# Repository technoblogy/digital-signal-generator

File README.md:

# Digital Signal Generator
A digital signal generator, based on an AVR16EB28, that generates a crystal accurate square wave of from 2Hz to 33.5MHz in precise steps of 2Hz. You can enter an exact frequency, or adjust the frequency continuously using a rotary encoder.

See http://www.technoblogy.com/show?5QE2.

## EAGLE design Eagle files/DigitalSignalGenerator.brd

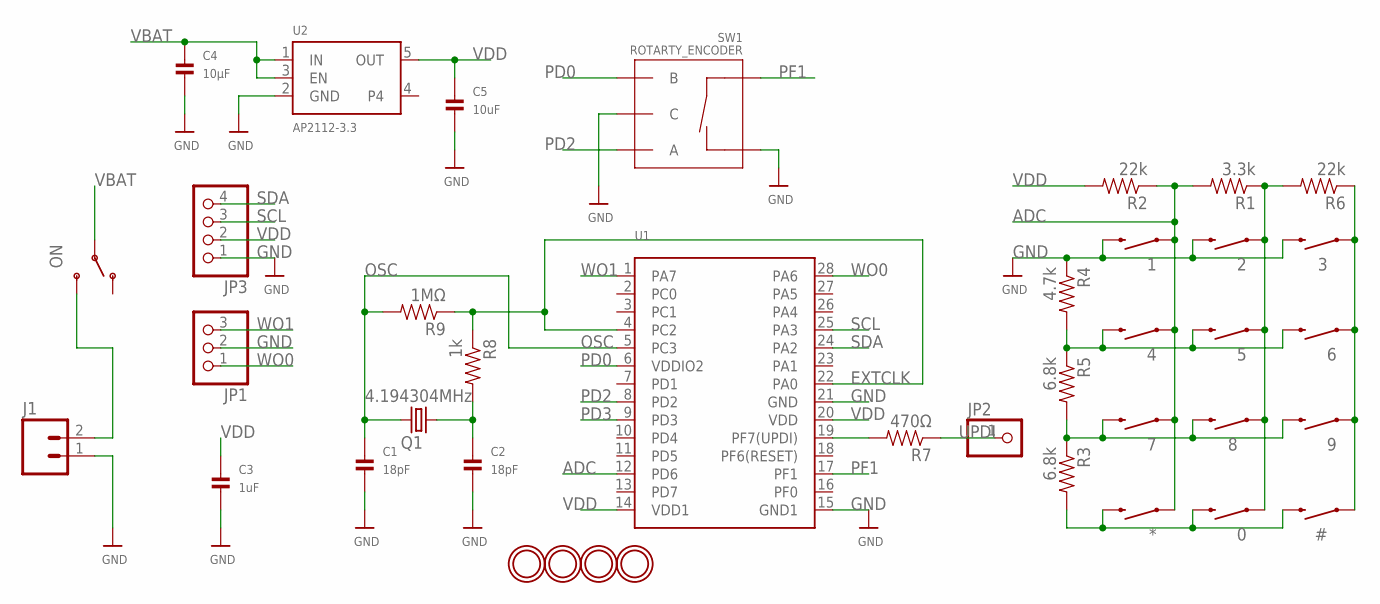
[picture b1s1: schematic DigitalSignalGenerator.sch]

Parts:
0, 1, 2, 3, 4, 5, 6, 7, 8, 9: SWITCH-MOMENTARY-2PTH; TACTILE-PTH
#: SWITCH-MOMENTARY-2PTH; TACTILE-PTH
*: SWITCH-MOMENTARY-2PTH; TACTILE-PTH
C1, C2: 18pF; _0805MP
C3: 1uF; _0805MP
C4: 10µF; _0805MP
C5: 10uF; _0805MP
J1: M02JST-PTH-VERT; JST-2-PTH-VERT
JP1: HEADER-1X3ROUND; 1X03_ROUND
JP2: PINHD-1X1CB; 1X01-CLEANBIG
JP3: HEADER-1X4ROUND; 1X04_ROUND
ON: SWITCH-SPDTKIT; SWITCH-SPDT_KIT
Q1: 4.194304MHz; CSM-7X-DU
R1: 3.3k; 0805
R2, R6: 22k; 0805
R3, R5: 6.8k; 0805
R4: 4.7k; 0805
R7: 470Ω; 0805
R8: 1k; 0805
R9: 1MΩ; 0805
SW1: ROTARTY_ENCODER; ROTARY_ENC_PLAIN
U1: AVR64DD28SSOPSSOP28; SSOP28DB
U2: AP2112-3.3; SOT23-5
U$9, U$10, U$11, U$12: MOUNTINGHOLE2.5; MOUNTINGHOLE_2.5_PLATED

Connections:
ADC: 1.1, 4.1, 7.1, *.1, R1.2, R2.1, U1.12 (PD6)
EXTCLK: R8.1, R9.1, U1.4 (PC2), U1.22 (PA0)
GND: 1.3 (2), 2.3 (2), 3.3 (2), C1.2, C2.2, C3.2, C4.2, C5.2, J1.1, JP1.2, JP3.1, R4.1, SW1.C, SW1.SW-, U1.15 (GND1), U1.21 (GND), U2.2 (GND)
unnamed: R7.2, U1.19 (PF7(UPDI))
unnamed: C2.1, Q1.2, R8.2
unnamed: J1.2, ON.3 (S)
unnamed: 0.3 (2), #.3 (2), *.3 (2), R3.2
unnamed: 4.3 (2), 5.3 (2), 6.3 (2), R4.2, R5.1
unnamed: 7.3 (2), 8.3 (2), 9.3 (2), R3.1, R5.2
unnamed: 0.1, 2.1, 5.1, 8.1, R1.1, R6.2
unnamed: 3.1, 6.1, 9.1, #.1, R6.1
OSC: C1.1, Q1.1, R9.2, U1.5 (PC3)
PD0: SW1.B, U1.6 (VDDIO2)
PD2: SW1.A, U1.8 (PD2)
PD3: U1.9 (PD3)
PF1: SW1.SW+, U1.17 (PF1)
SCL: JP3.3, U1.25 (PA3)
SDA: JP3.4, U1.24 (PA2)
UPDI: JP2.1, R7.1
VBAT: C4.1, ON.2, U2.1 (IN), U2.3 (EN)
VDD: C3.1, C5.1, JP3.2, R2.2, U1.14 (VDD1), U1.20 (VDD), U2.5 (OUT)
WO0: JP1.1, U1.28 (PA6)
WO1: JP1.3, U1.1 (PA7)

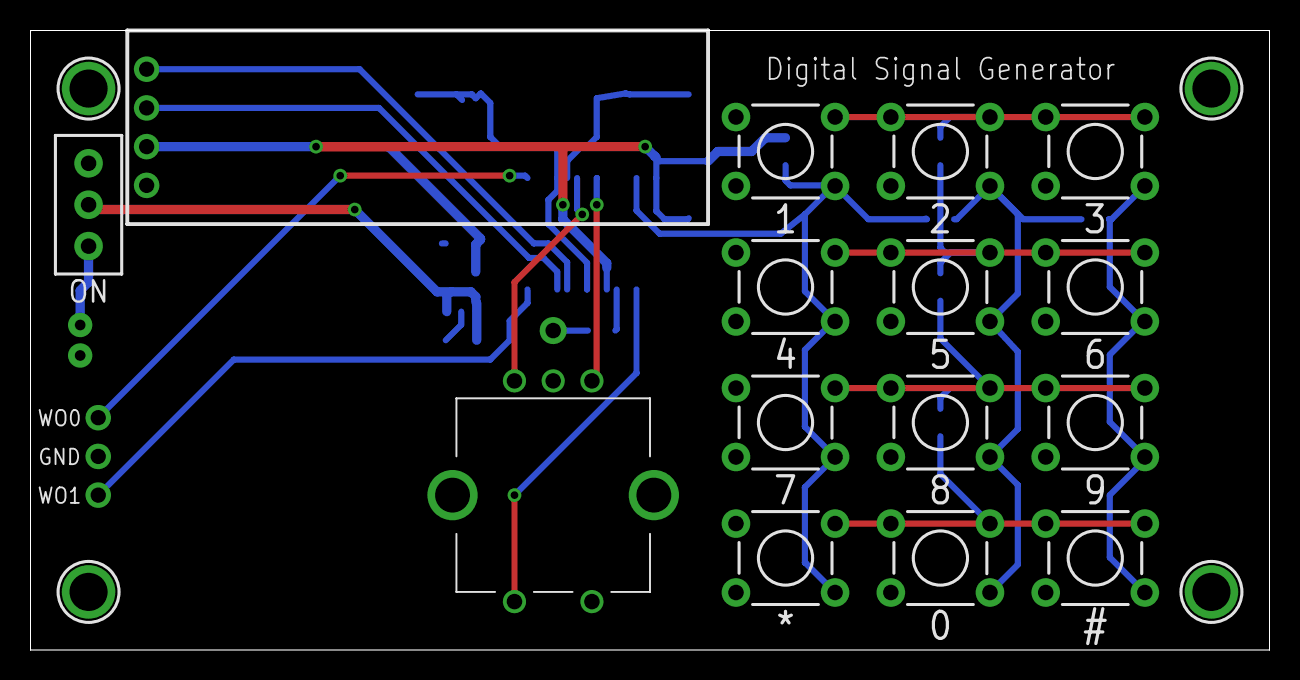
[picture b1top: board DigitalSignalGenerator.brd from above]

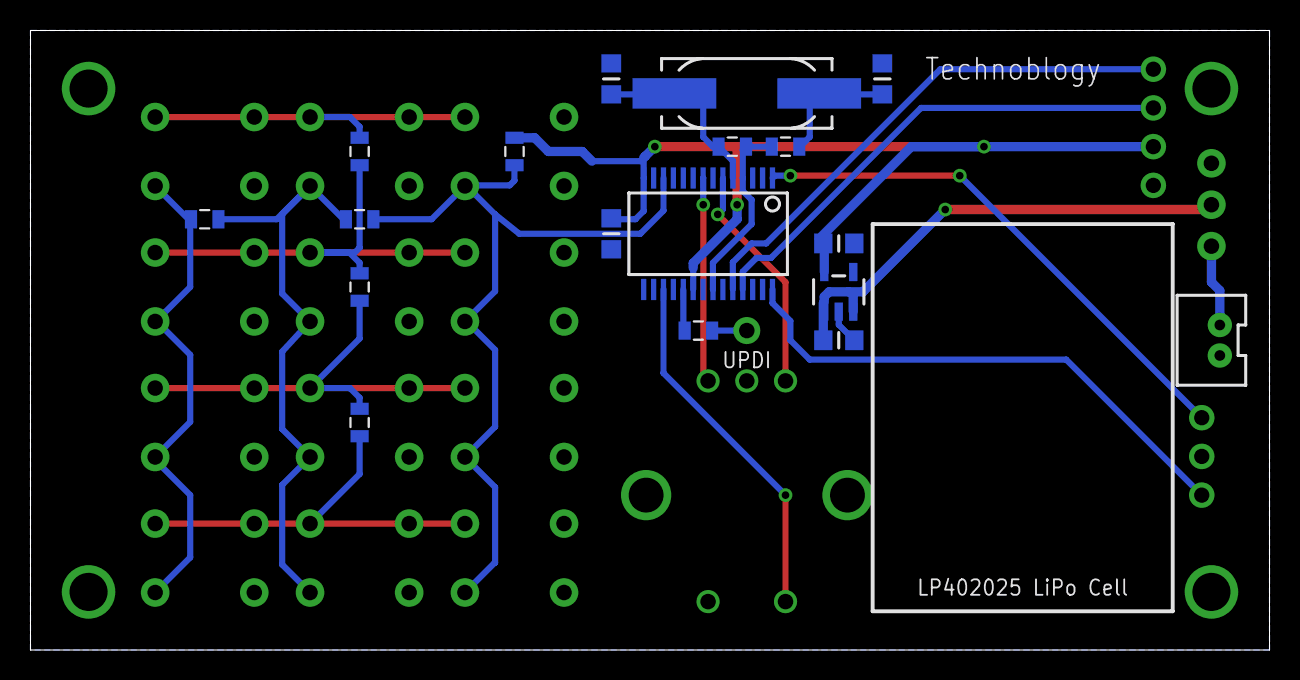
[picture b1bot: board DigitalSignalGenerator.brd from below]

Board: 2 copper layers, 81.3 x 40.6 mm, 39 parts (18 on the bottom side), 22 nets.

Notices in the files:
parts and their libraries:
SparkFun-Electromechanical: Licensing: Creative Commons ShareAlike 4.0 International - https://creativecommons.org/licenses/by-sa/4.0
SparkFun-Resistors: Licensing: CC v3.0 Share-Alike You are welcome to use this library for commercial purposes.
